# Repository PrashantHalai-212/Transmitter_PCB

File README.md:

# Transmitter_PCB

A Batman-inspired Batarang-shaped wireless transmitter board featuring an ATmega328P microcontroller, NRF24L01 module, and onboard CH340G USB programmer. Essentially an Arduino with integrated wireless capability and custom PCB design shaped like Batman's iconic throwing weapon.

## PCB Design

## Features

- **ATmega328P Microcontroller** - Same as Arduino
- **NRF24L01 Wireless Module** - 2.4GHz RF Communication
- **CH340G USB Programmer** - Direct programming without external programmer
- **Batarang Shape** - Batman-inspired custom PCB design
- **Full Arduino Compatibility** - Use standard Arduino sketches
- **All Supporting Components** - Crystal oscillator, capacitors, USB connector

## Files

- `Transmitter_PCB.kicad_sch` - Schematic design
- `Transmitter_PCB.kicad_pcb` - PCB layout
- `Transmitter_PCB.kicad_pro` - Project file

## Requirements

- KiCad 6.0 or later
- Arduino IDE (for programming)

## License

MIT

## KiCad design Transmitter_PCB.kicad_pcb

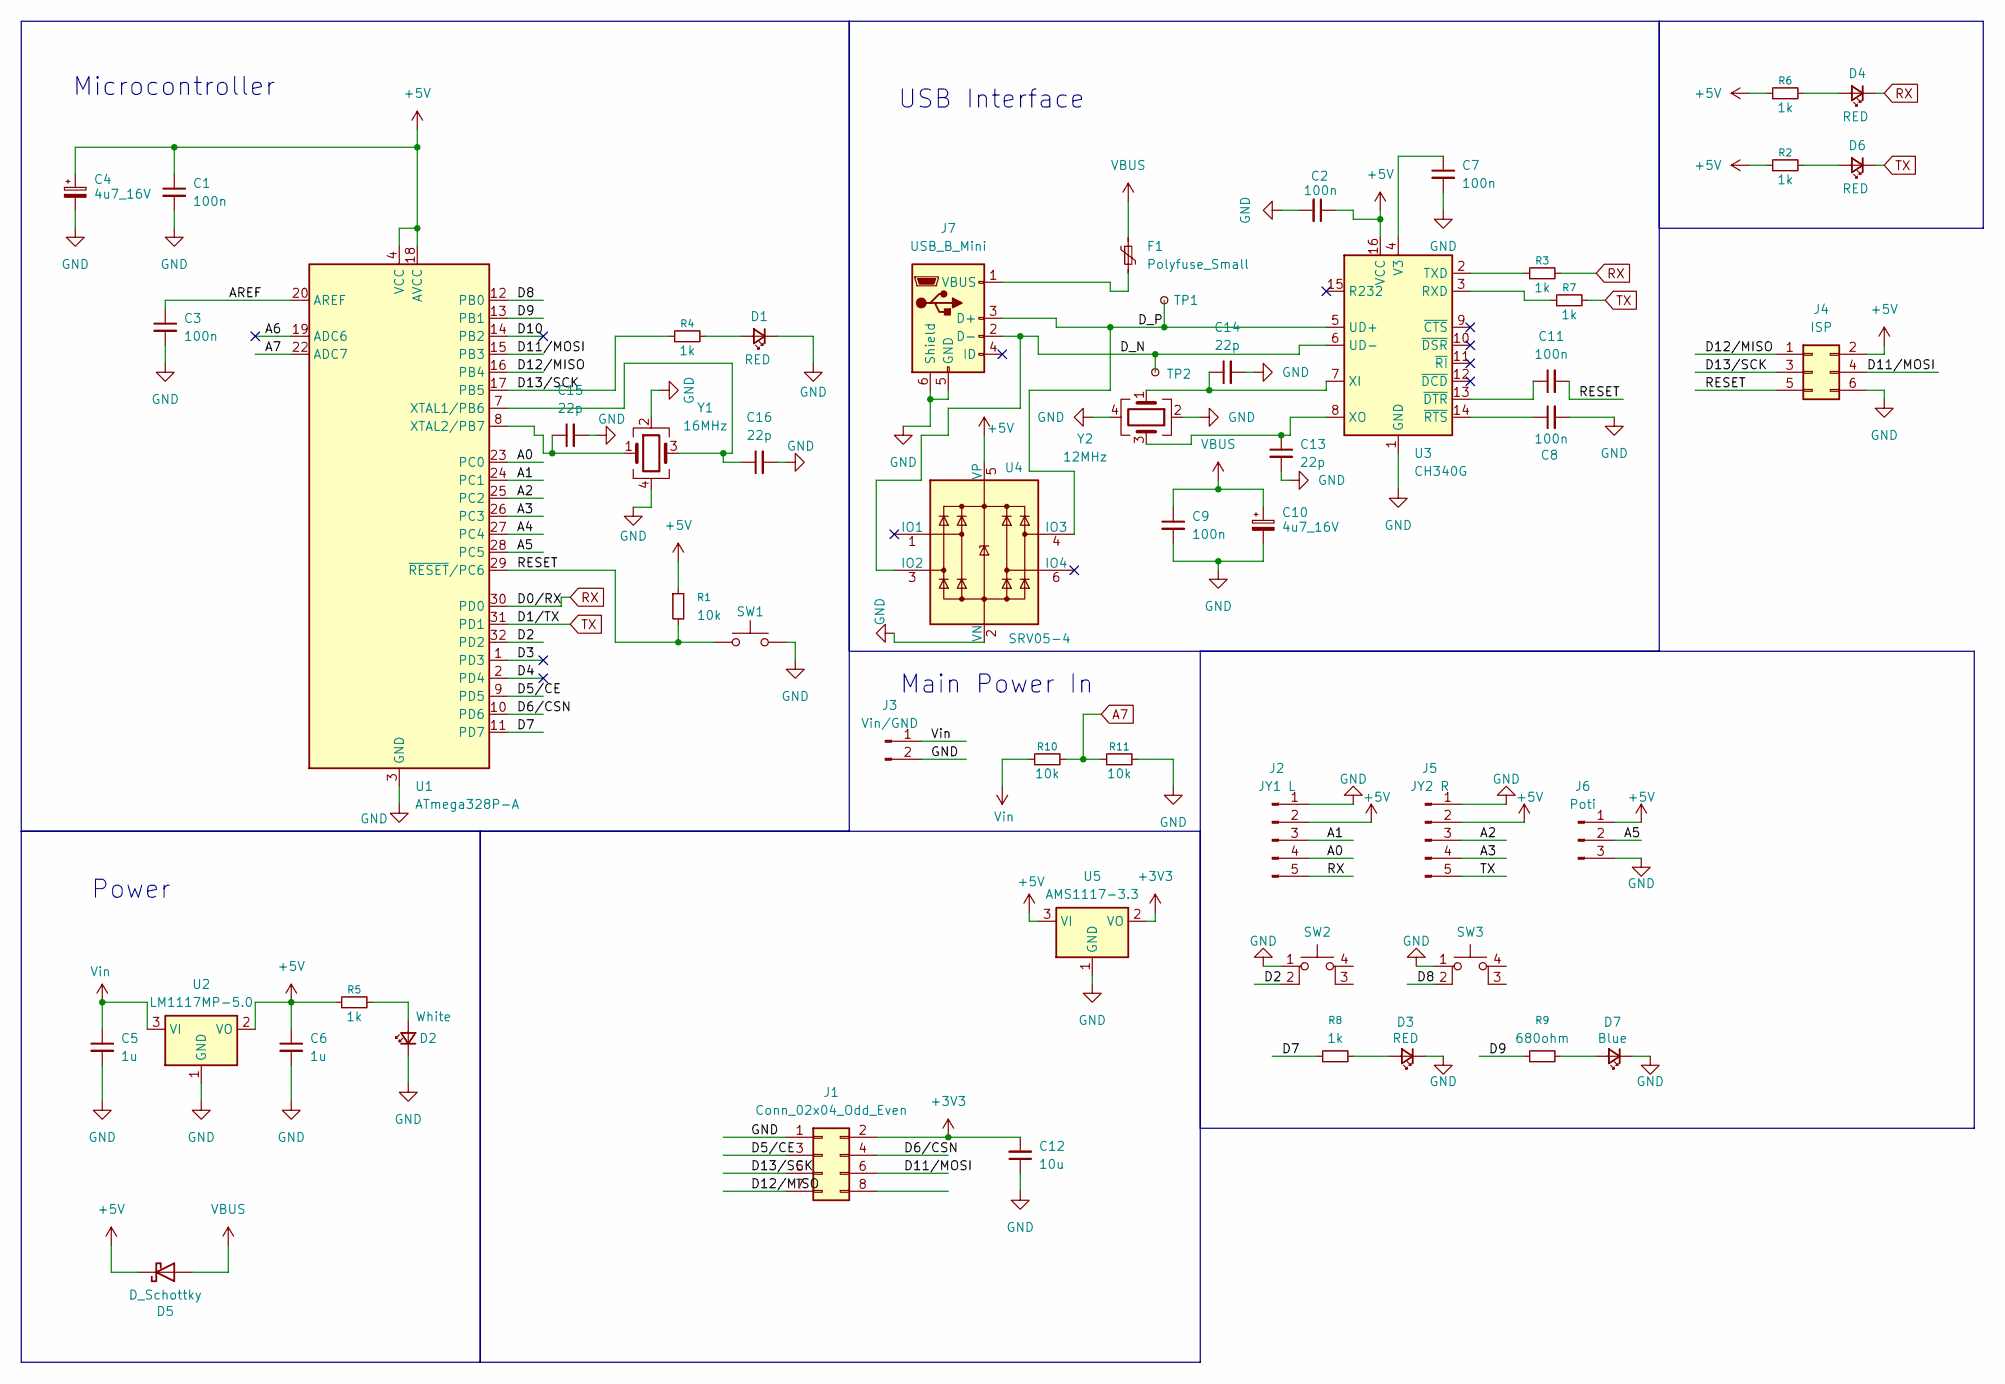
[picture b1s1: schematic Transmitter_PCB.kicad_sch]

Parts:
C1, C2, C3, C7, C8, C9, C11: 100n; C_0603_1608Metric
C4, C10: 4u7_16V; CP_EIA-3216-10_Kemet-I
C5, C6: 1u; C_0603_1608Metric
C12: 10u; C_0603_1608Metric
C13, C14, C15, C16: 22p; C_0603_1608Metric
D1, D4, D6: RED; LED_0603_1608Metric_Pad1.05x0.95mm_HandSolder
D2: White; LED_0603_1608Metric_Pad1.05x0.95mm_HandSolder
D3: RED; LED_0805_2012Metric
D5: D_Schottky; D_SOD-123
D7: Blue; LED_0805_2012Metric
F1: Polyfuse_Small; Fuse_1206_3216Metric
J1: Conn_02x04_Odd_Even; PinHeader_2x04_P2.54mm_Vertical
J2: JY1 L; PinHeader_1x05_P2.54mm_Vertical
J3: Vin/GND; PinHeader_1x02_P2.54mm_Vertical
J4: ISP; PinHeader_2x03_P2.54mm_Vertical
J5: JY2 R; PinHeader_1x05_P2.54mm_Vertical
J6: Poti; PinHeader_1x03_P2.54mm_Vertical
J7: USB_B_Mini; USB_Mini-B_Lumberg_2486_01_Horizontal
R1, R10, R11: 10k; R_0603_1608Metric
R2, R3, R4, R5, R6, R7, R8: 1k; R_0603_1608Metric
R9: 680ohm; R_0603_1608Metric
SW1: SW_Push; SW_SPST_CK_RS282G05A3
SW2, SW3: SW_Push_1P1T_NO_CK_KSC6xxG
TP1, TP2: TestPoint_Small; TestPoint_Pad_D1.0mm
U1: ATmega328P-A; TQFP-32_7x7mm_P0.8mm
U2: LM1117MP-5.0; SOT-223-3_TabPin2
U3: CH340G; SOIC-16_3.9x9.9mm_P1.27mm
U4: SRV05-4; SOT-23-6
U5: AMS1117-3.3; SOT-223-3_TabPin2
Y1: 16MHz; Crystal_SMD_3225-4Pin_3.2x2.5mm
Y2: 12MHz; Crystal_SMD_3225-4Pin_3.2x2.5mm

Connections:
+3V3: C12.2, J1.2, U5.2 (VO)
+5V: C1.1, C2.1, C4.1, C6.1, D5.1 (K), J2.2, J4.2, J5.2, J6.1, R1.1, R2.1, R5.1, R6.1, U1.4 (VCC), U1.6 (VCC), U1.18 (AVCC), U2.2 (VO), U3.16 (VCC), U4.5 (VP), U5.3 (VI)
/A0: J2.4, U1.23 (PC0)
/A1: J2.3, U1.24 (PC1)
/A2: J5.3, U1.25 (PC2)
/A3: J5.4, U1.26 (PC3)
/A4: U1.27 (PC4)
/A5: J6.2, U1.28 (PC5)
/A6: U1.19 (ADC6)
/AREF: C3.1, U1.20 (AREF)
/D2: SW2.2, U1.32 (PD2)
/D3: U1.1 (PD3)
/D4: U1.2 (PD4)
/D5/CE: J1.3, U1.9 (PD5)
/D6/CSN: J1.4, U1.10 (PD6)
/D7: R8.1, U1.11 (PD7)
/D8: SW3.2, U1.12 (PB0)
/D9: R9.1, U1.13 (PB1)
/D10: U1.14 (PB2)
/D11/MOSI: J1.6, J4.4, U1.15 (PB3)
/D12/MISO: J1.7, J4.1, U1.16 (PB4)
/D13/SCK: J1.5, J4.3, R4.1, U1.17 (PB5)
/D_N: J7.2 (D-), TP2.1, U3.6 (UD-), U4.3 (IO2)
/D_P: J7.3 (D+), TP1.1, U3.5 (UD+), U4.4 (IO3)
/RESET: C11.2, J4.5, R1.2, SW1.1, U1.29 (~RESET/PC6)
A7: R10.2, R11.1, U1.22 (ADC7)
GND: C1.2, C2.2, C3.2, C4.2, C5.2, C6.2, C7.2, C8.2, C9.2, C10.2, C12.1, C13.2, C14.2, C15.2, C16.2, D1.1 (K), D2.1 (K), D3.1 (K), D7.1 (K), J1.1, J2.1, J3.2, J4.6, J5.1, J6.3, J7.5 (GND), J7.6 (Shield), R11.2, SW1.2, SW2.1, SW3.1, U1.3 (GND), U1.5 (GND), U1.21 (GND), U2.1 (GND), U3.1 (GND), U4.2 (VN), U5.1 (GND), Y1.2, Y1.4, Y2.2, Y2.4
unnamed: D1.2 (A), R4.2
unnamed: D2.2 (A), R5.2
unnamed: D3.2 (A), R8.2
unnamed: D4.2 (A), R6.2
unnamed: D6.2 (A), R2.2
unnamed: D7.2 (A), R9.2
unnamed: F1.2, J7.1 (VBUS)
unnamed: C16.1, U1.7 (XTAL1/PB6), Y1.3
unnamed: C15.1, U1.8 (XTAL2/PB7), Y1.1
unnamed: R7.1, U3.3 (RXD)
unnamed: R3.1, U3.2 (TXD)
unnamed: C7.1, U3.4 (V3)
unnamed: C14.1, U3.7 (XI), Y2.1
unnamed: C13.1, U3.8 (XO), Y2.3
unnamed: C11.1, U3.13 (~DTR)
unnamed: C8.1, U3.14 (~RTS)
RX: D4.1 (K), J2.5, R3.2, U1.30 (PD0)
TX: D6.1 (K), J5.5, R7.2, U1.31 (PD1)
VBUS: C9.1, C10.1, D5.2 (A), F1.1
Vin: C5.1, J3.1, R10.1, U2.3 (VI)

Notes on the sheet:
Power
Main Power In
USB Interface
Microcontroller

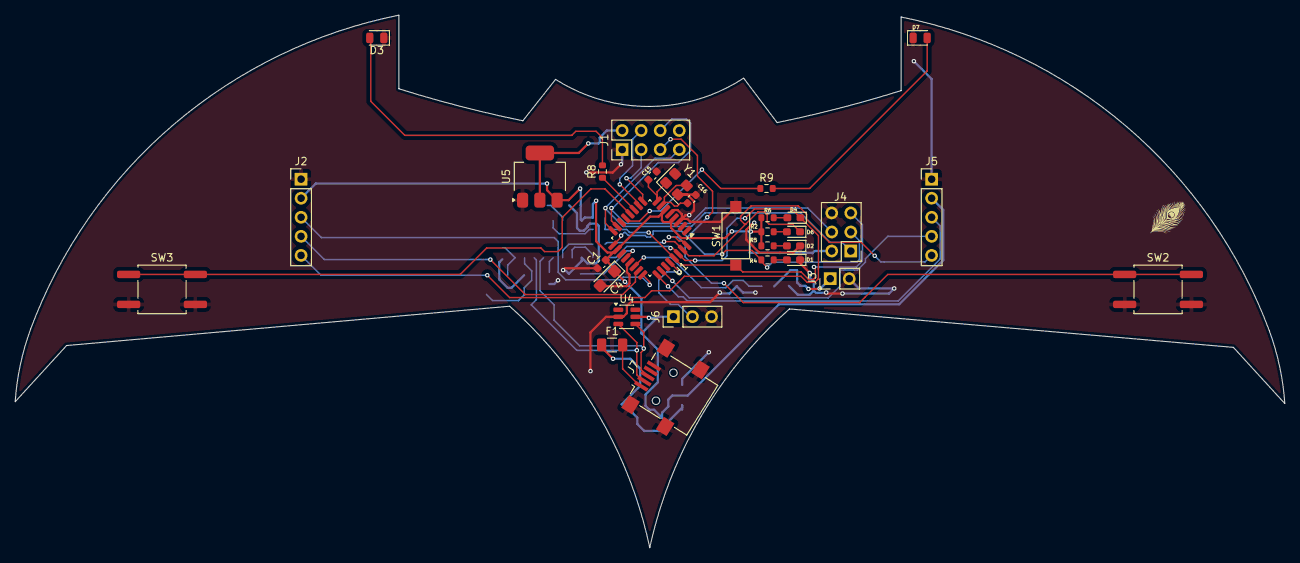
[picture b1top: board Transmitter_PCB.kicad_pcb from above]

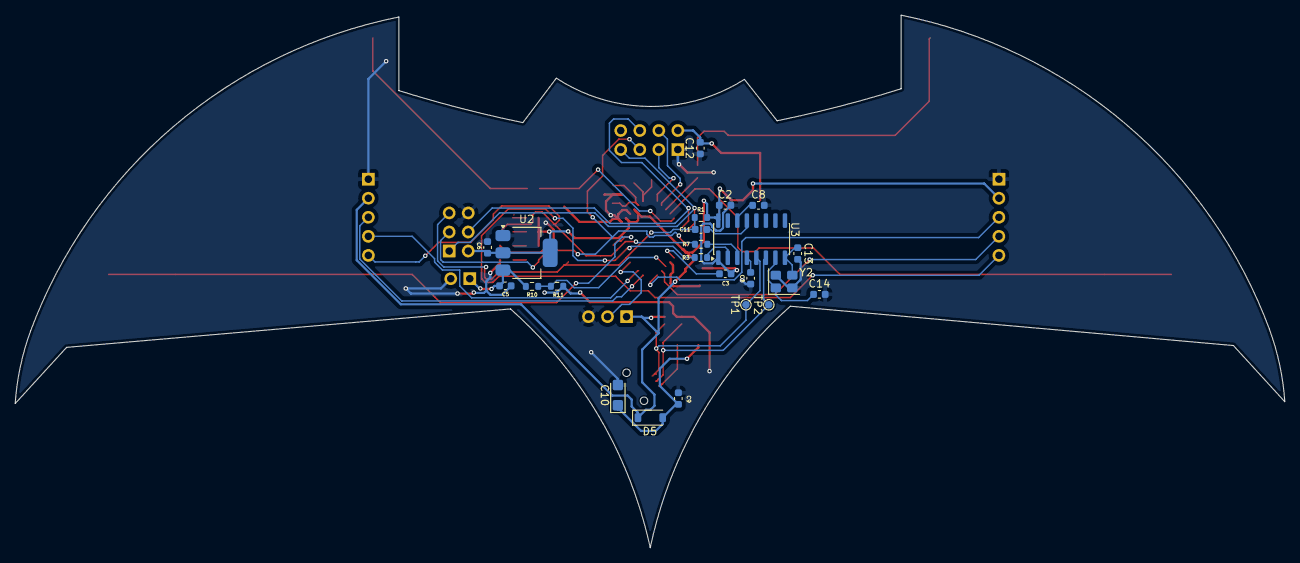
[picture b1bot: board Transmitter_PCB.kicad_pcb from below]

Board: 2 copper layers, 169.4 x 71.0 mm, 54 parts (23 on the bottom side), 42 nets.

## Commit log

2026-05-23 Initial commit: Add Batarang transmitter KiCAD project
2026-05-23 Add PCB render image
2026-05-23 Update README with project details
